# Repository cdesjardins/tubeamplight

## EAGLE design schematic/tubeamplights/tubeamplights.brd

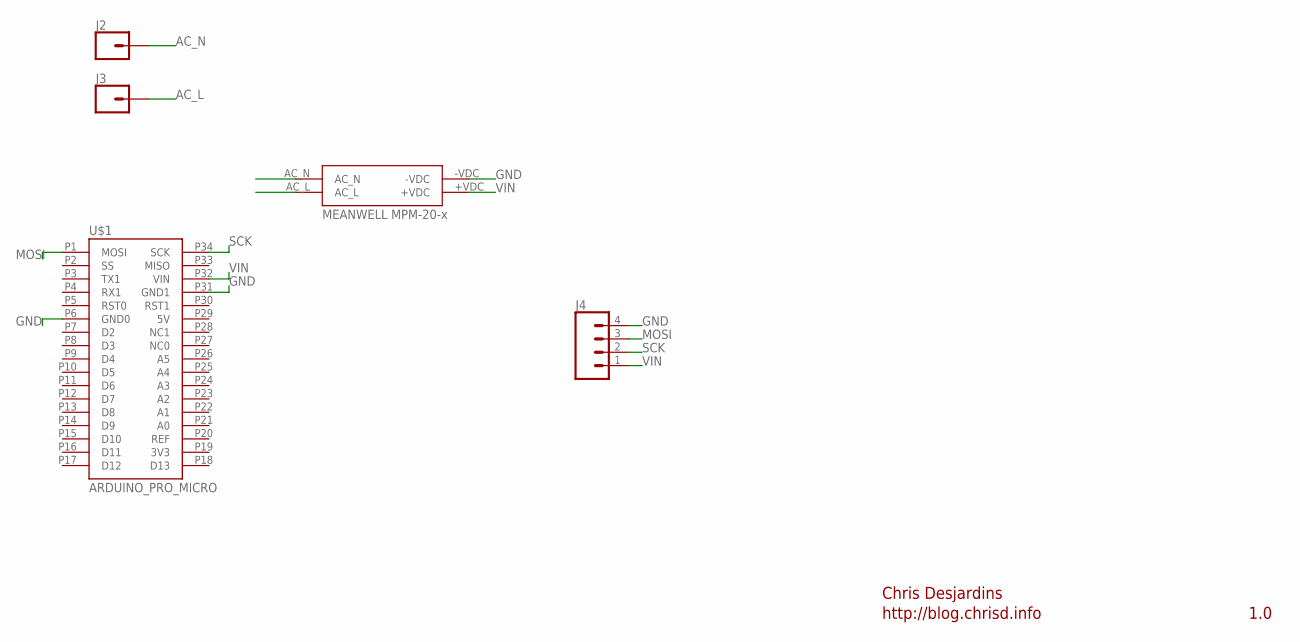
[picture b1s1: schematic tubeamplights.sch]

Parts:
J2, J3: CONN_01PTH_2MM; 1X01_2MM
J4: CONN_04; 1X04
U$1: ARDUINO_PRO_MICRO
U$2: MPM-20-X

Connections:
3V3: U$1.P19 (3V3)
5V: U$1.P29 (5V)
AC_L: J3.1, U$2.AC_L
AC_N: J2.1, U$2.AC_N
GND: J4.4, U$1.P6 (GND0), U$1.P31 (GND1), U$2.-VDC
MOSI: J4.3, U$1.P1 (MOSI)
REF: U$1.P20 (REF)
SCK: J4.2, U$1.P34 (SCK)
VIN: J4.1, U$1.P32 (VIN), U$2.+VDC

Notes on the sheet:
Chris Desjardins
1.0
http://blog.chrisd.info

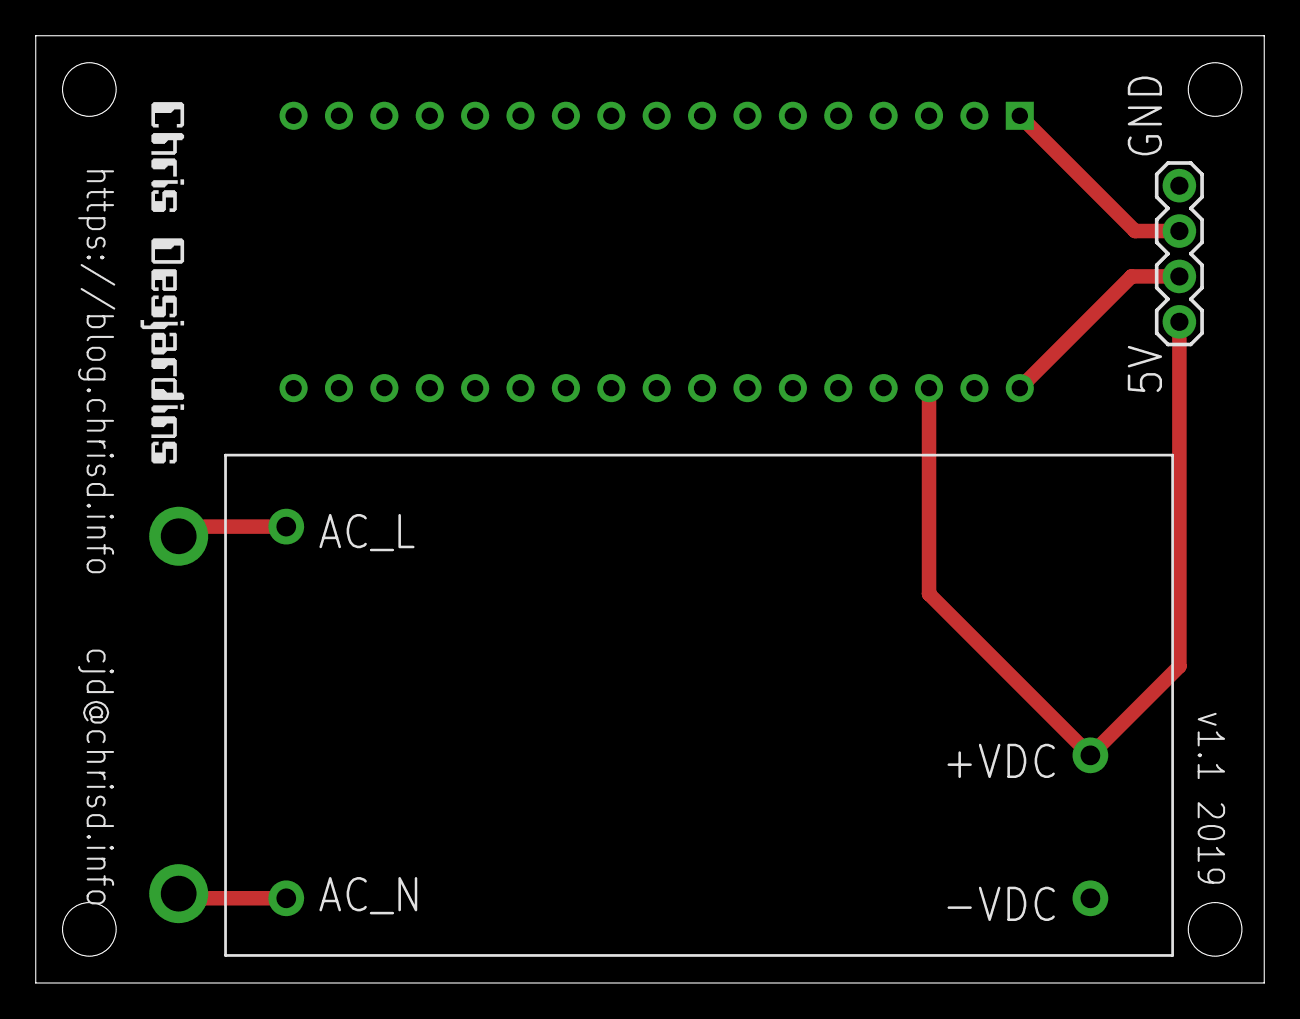
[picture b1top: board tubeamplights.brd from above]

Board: 2 copper layers, 68.8 x 53.0 mm, 6 parts (0 on the bottom side), 6 nets.

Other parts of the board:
U$3: LOGO

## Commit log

2019-07-07 Add code for dotstar lights
2019-07-07 Add some flash to init sequence
2019-07-07 Add board design
2019-07-07 Add version and date to board
2019-07-07 Add mounting holes
2019-08-04 Fix the reg footprint

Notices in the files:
parts and their libraries:
SparkFun-Connectors: Licensing: Creative Commons ShareAlike 4.0 International - https://creativecommons.org/licenses/by-sa/4.0
